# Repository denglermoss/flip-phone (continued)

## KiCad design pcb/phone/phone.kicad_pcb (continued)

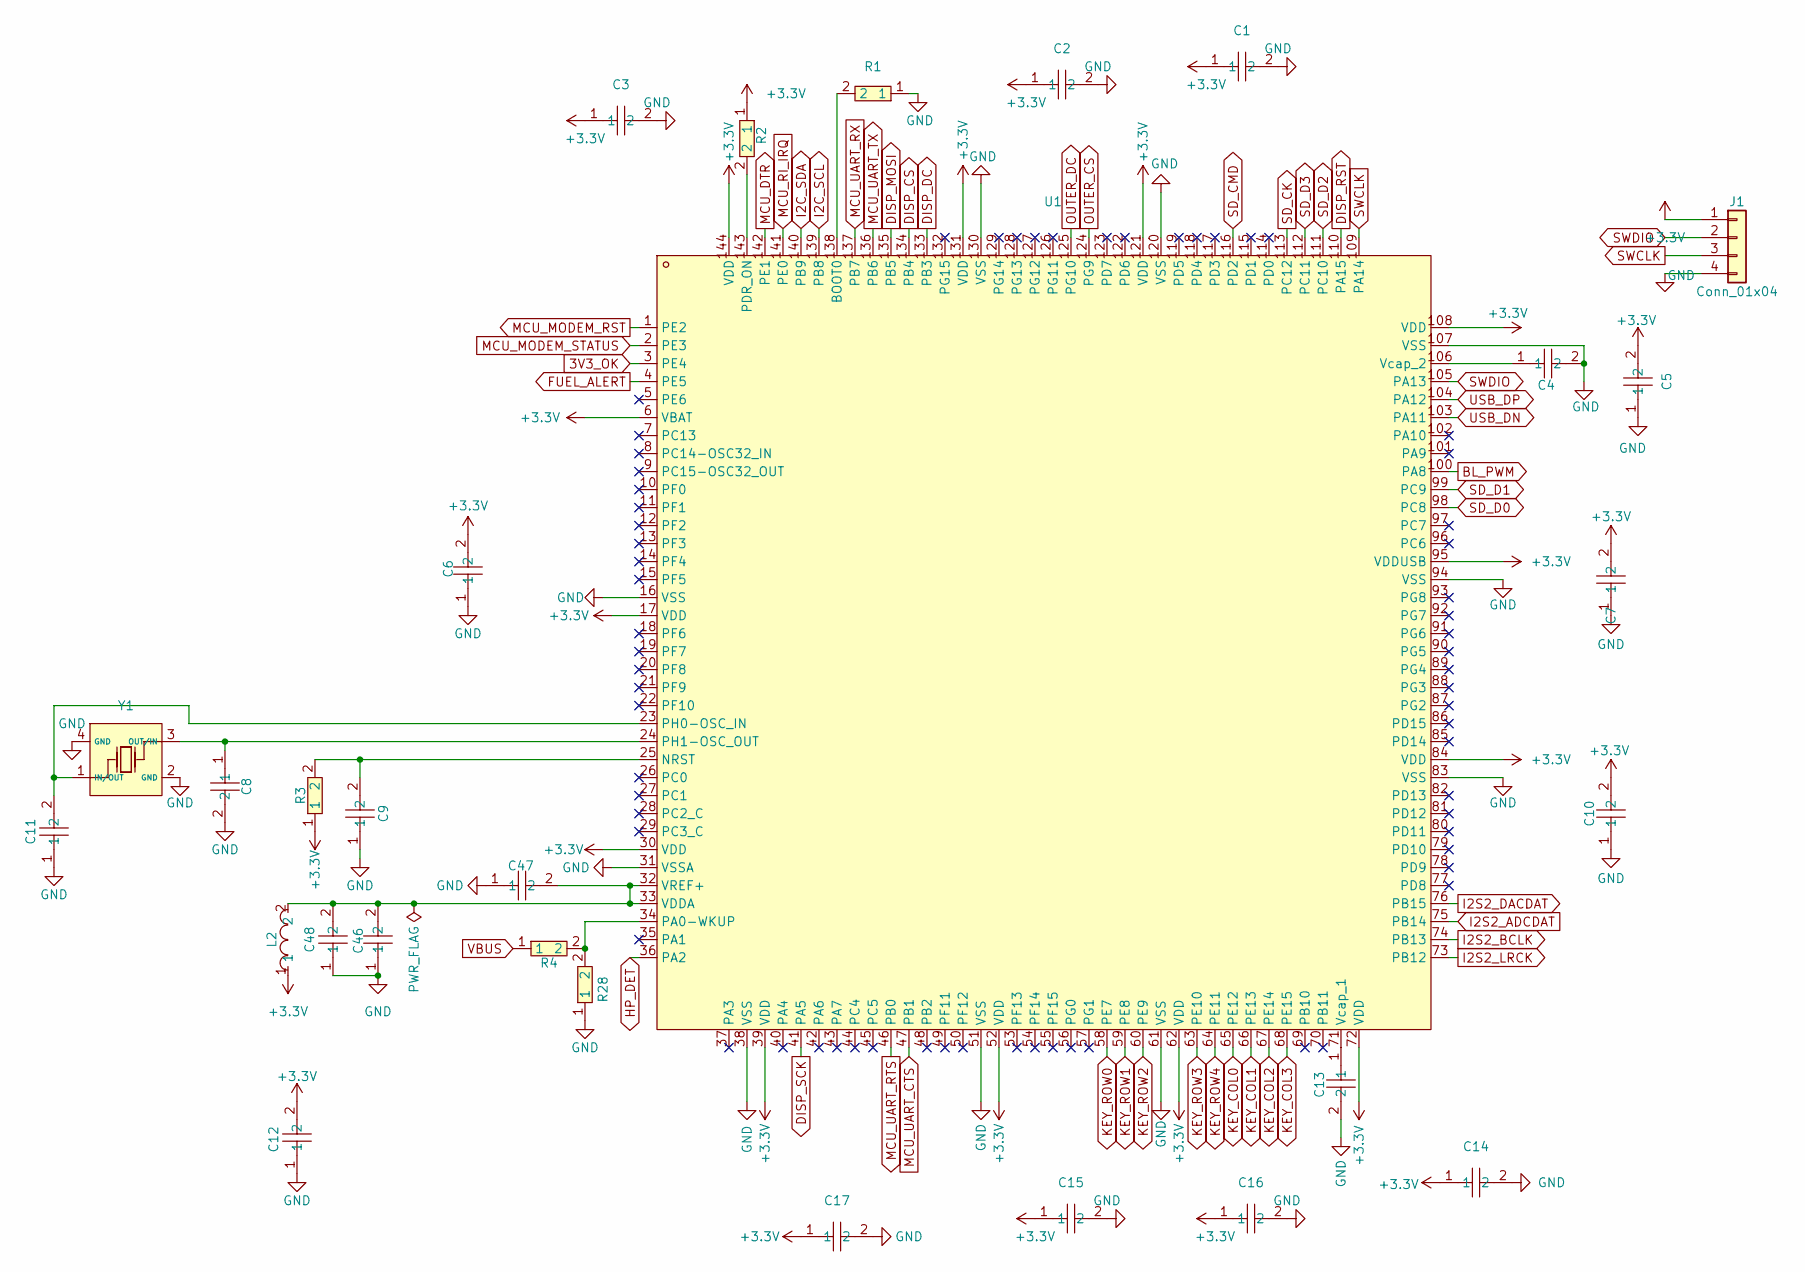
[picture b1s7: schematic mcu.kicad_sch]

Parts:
C1, C2, C3, C5, C6, C7, C9, C10, C12, C14, C15, C16, C17: 100nF; C0603
C4, C13: 2.2uF; C0603
C8, C11: 22pF; C0603
C46, C47: CC0603KRX7R9BB104; C0603; MPN CC0603KRX7R9BB104; LCSC Part C14663
C48: 1uF; C0603; MPN GRM188R61C105KA93D; LCSC Part C77404
J1: Conn_01x04; PinHeader_1x04_P2.54mm_Vertical
L2: BLM18KG601SN1D; L0603; MPN BLM18KG601SN1D; LCSC Part C85833
R1, R2, R3: 10k; C0603
R4: 100k; R0603
R28: RC0603FR-0768KL; R0603; MPN RC0603FR-0768KL; LCSC Part C114633
U1: STM32H743ZIT6; LQFP-144_L20.0-W20.0-P0.50-LS22.0-BL
Y1: ECS-80-12-33Q-GN-TR; CRYSTAL-SMD_4P-L3.2-W2.5-BL

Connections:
3V3_OK: U1.3 (PE4); also elsewhere on the board
+3.3V: C1.1, C2.1, C3.1, C5.2, C6.2, C7.2, C10.2, C12.2, C14.1, C15.1, C16.1, C17.1, J1.1, L2.1, R2.1, R3.1, U1.6 (VBAT), U1.17 (VDD), U1.30 (VDD), U1.39 (VDD), U1.52 (VDD), U1.62 (VDD), U1.72 (VDD), U1.84 (VDD), U1.95 (VDDUSB), U1.108 (VDD), U1.121 (VDD), U1.131 (VDD), U1.144 (VDD); also elsewhere on the board
BL_PWM: U1.100 (PA8); also elsewhere on the board
DISP_CS: U1.134 (PB4); also elsewhere on the board
DISP_DC: U1.133 (PB3); also elsewhere on the board
DISP_MOSI: U1.135 (PB5); also elsewhere on the board
DISP_RST: U1.110 (PA15); also elsewhere on the board
DISP_SCK: U1.41 (PA5); also elsewhere on the board
FUEL_ALERT: U1.4 (PE5); also elsewhere on the board
GND: C1.2, C2.2, C3.2, C4.2, C5.1, C6.1, C7.1, C8.2, C9.1, C10.1, C11.1, C12.1, C13.2, C14.2, C15.2, C16.2, C17.2, C46.1, C47.1, C48.1, J1.4, R1.1, R28.1, U1.16 (VSS), U1.31 (VSSA), U1.38 (VSS), U1.51 (VSS), U1.61 (VSS), U1.83 (VSS), U1.94 (VSS), U1.107 (VSS), U1.120 (VSS), U1.130 (VSS), Y1.2 (GND), Y1.4 (GND); also elsewhere on the board
HP_DET: U1.36 (PA2)
I2C_SCL: U1.139 (PB8); also elsewhere on the board
I2C_SDA: U1.140 (PB9); also elsewhere on the board
I2S2_ADCDAT: U1.75 (PB14); also elsewhere on the board
I2S2_BCLK: U1.74 (PB13); also elsewhere on the board
I2S2_DACDAT: U1.76 (PB15); also elsewhere on the board
I2S2_LRCK: U1.73 (PB12); also elsewhere on the board
KEY_COL0: U1.65 (PE12); also elsewhere on the board
KEY_COL1: U1.66 (PE13); also elsewhere on the board
KEY_COL2: U1.67 (PE14); also elsewhere on the board
KEY_COL3: U1.68 (PE15); also elsewhere on the board
KEY_ROW0: U1.58 (PE7); also elsewhere on the board
KEY_ROW1: U1.59 (PE8); also elsewhere on the board
KEY_ROW2: U1.60 (PE9); also elsewhere on the board
KEY_ROW3: U1.63 (PE10); also elsewhere on the board
KEY_ROW4: U1.64 (PE11); also elsewhere on the board
MCU_DTR: U1.142 (PE1); also elsewhere on the board
MCU_MODEM_RST: U1.1 (PE2); also elsewhere on the board
MCU_MODEM_STATUS: U1.2 (PE3); also elsewhere on the board
MCU_RI_IRQ: U1.141 (PE0); also elsewhere on the board
MCU_UART_CTS: U1.47 (PB1); also elsewhere on the board
MCU_UART_RTS: U1.46 (PB0); also elsewhere on the board
MCU_UART_RX: U1.137 (PB7); also elsewhere on the board
MCU_UART_TX: U1.136 (PB6); also elsewhere on the board
unnamed: R1.2, U1.138 (BOOT0)
unnamed: C9.2, R3.2, U1.25 (NRST)
unnamed: R4.2, R28.2, U1.34 (PA0-WKUP)
unnamed: R2.2, U1.143 (PDR_ON)
unnamed: C11.2, U1.23 (PH0-OSC_IN), Y1.1 (IN/OUT)
unnamed: C8.1, U1.24 (PH1-OSC_OUT), Y1.3 (OUT/IN)
unnamed: C46.2, C47.2, C48.2, L2.2, U1.32 (VREF+), U1.33 (VDDA)
unnamed: C13.1, U1.71 (Vcap_1)
unnamed: C4.1, U1.106 (Vcap_2)
OUTER_CS: U1.124 (PG9); also elsewhere on the board
OUTER_DC: U1.125 (PG10); also elsewhere on the board
SD_CK: U1.113 (PC12); also elsewhere on the board
SD_CMD: U1.116 (PD2); also elsewhere on the board
SD_D0: U1.98 (PC8); also elsewhere on the board
SD_D1: U1.99 (PC9); also elsewhere on the board
SD_D2: U1.111 (PC10); also elsewhere on the board
SD_D3: U1.112 (PC11); also elsewhere on the board
SWCLK: J1.3, U1.109 (PA14)
SWDIO: J1.2, U1.105 (PA13)
USB_DN: U1.103 (PA11); also elsewhere on the board
USB_DP: U1.104 (PA12); also elsewhere on the board
VBUS: R4.1; also elsewhere on the board

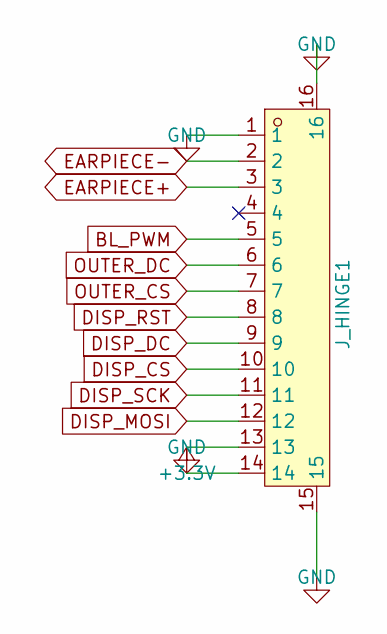
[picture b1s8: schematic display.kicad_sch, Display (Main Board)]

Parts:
J_HINGE1: 0.5K-HX-14PWB; FPC-SMD_14P-P0.50_HDGC_0.5K-HX-14PWB

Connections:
+3.3V: J_HINGE1.14; also elsewhere on the board
BL_PWM: J_HINGE1.5; also elsewhere on the board
DISP_CS: J_HINGE1.10; also elsewhere on the board
DISP_DC: J_HINGE1.9; also elsewhere on the board
DISP_MOSI: J_HINGE1.12; also elsewhere on the board
DISP_RST: J_HINGE1.8; also elsewhere on the board
DISP_SCK: J_HINGE1.11; also elsewhere on the board
EARPIECE+: J_HINGE1.3; also elsewhere on the board
EARPIECE-: J_HINGE1.2; also elsewhere on the board
GND: J_HINGE1.1, J_HINGE1.13, J_HINGE1.15, J_HINGE1.16; also elsewhere on the board
OUTER_CS: J_HINGE1.7; also elsewhere on the board
OUTER_DC: J_HINGE1.6; also elsewhere on the board

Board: 2 copper layers, 130 parts (0 on the bottom side), 104 nets, no tracks yet.

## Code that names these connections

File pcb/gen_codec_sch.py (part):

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    apw(net,px+off,py,90,f"#PWR{pwr_ctr}"); aw(px,py,px+off,py)

print("Wiring PCM/I2S-1...")
for pin,label,shape in [(30,"PCM_IN","output"),(31,"PCM_OUT","input"),(32,"PCM_SYNC","bidirectional"),(33,"PCM_CLK","bidirectional")]:
    px,py=u3p(pin); aw(px,py,px+7.06,py); agl(label,px+7.06,py,0,shape)

print("Wiring I2C...")
for pin,label in [(35,"I2C_SCL"),(36,"I2C_SDA")]:
    px,py=u3p(pin); aw(px,py,px+7.06,py); agl(label,px+7.06,py,0,"bidirectional")
for rx,ry,label in [(R12_X,R12_Y,"I2C_SCL"),(R13_X,R13_Y,"I2C_SDA")]:
    p1=cpp(rx,ry,1); p2=cpp(rx,ry,2)
    apw("+1V8",p1[0],p1[1]-5.08,0,f"#PWR{pwr_ctr}"); aw(p1[0],p1[1],p1[0],p1[1]-5.08)
    aw(p2[0],p2[1],p2[0]+5.08,p2[1]); agl(label,p2[0]+5.08,p2[1],0,"bidirectional")
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for cp,tx,bx in [(29,1,180),(28,3,185),(27,4,190),(26,5,195)]:
    cx,cy=u3p(cp); ax,ay=u9p(tx)
    aw(cx,cy,bx,cy); aw(bx,cy,bx,ay); aw(bx,ay,ax,ay)
for tp,label,shape in [(20,"I2S2_BCLK","input"),(18,"I2S2_LRCK","input"),(17,"I2S2_DACDAT","input"),(16,"I2S2_ADCDAT","output")]:
    bx,by=u9p(tp); aw(bx,by,bx+7.62,by); agl(label,bx+7.62,by,0,shape)

print("Wiring TXB0108 power...")
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
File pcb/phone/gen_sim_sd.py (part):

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        comp += fpwr('power:GND', wx, py, 0, '#PWR%d' % pc, sp); pc += 1

    # === U10 (ESD for SIM) wiring ===
    # Pin 1 (IO1) -> USIM_DATA
    px, py = pin_pos(U10_X, U10_Y, ESD_PINS[1])
    wx = px - STUB
    wires += fw(px, py, wx, py)
    labels += fgl('USIM_DATA', 'bidirectional', wx, py, 180)

    # Pin 2 (GND)
    px, py = pin_pos(U10_X, U10_Y, ESD_PINS[2])
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    wires += fw(px, py, wx, py)
    comp += fpwr('power:GND', wx, py, 0, '#PWR%d' % pc, sp); pc += 1

    # Pin 3 (IO2) -> USIM_RST
    px, py = pin_pos(U10_X, U10_Y, ESD_PINS[3])
    wx = px - STUB
    wires += fw(px, py, wx, py)
    labels += fgl('USIM_RST', 'bidirectional', wx, py, 180)

    # Pin 4 (IO3) -> USIM_CLK
    px, py = pin_pos(U10_X, U10_Y, ESD_PINS[4])
    wx = px + STUB
    wires += fw(px, py, wx, py)
    labels += fgl('USIM_CLK', 'bidirectional', wx, py, 0)

    # Pin 5 (IO4) -> USIM_VDD
    px, py = pin_pos(U10_X, U10_Y, ESD_PINS[5])
    wx = px + STUB
    wires += fw(px, py, wx, py)
    labels += fgl('USIM_VDD', 'bidirectional', wx, py, 0)

    # Pin 6 (IO5) - no connect (unused)
    px, py = pin_pos(U10_X, U10_Y, ESD_PINS[6])
    ncs += fnc(px, py)

    # === C38 (SIM decoupling) wiring ===
    # Pin 1 (top, original offset -5.08,0 with rot 90 -> above center) -> USIM_VDD
    px, py = pin_pos(C38_X, C38_Y, (-5.08, 0), 90)
    wy = py - STUB
    wires += fw(px, py, px, wy)
    labels += fgl('USIM_VDD', 'bidirectional', px, wy, 90)

    # Pin 2 (bottom, original offset 5.08,0 with rot 90 -> below center) -> GND
    px, py = pin_pos(C38_X, C38_Y, (5.08, 0), 90)
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    comp += fpwr('power:GND', px, wy, 0, '#PWR%d' % pc, sp); pc += 1

    # === R15 (SIM data pull-up) wiring ===
    # Pin 1 (left) -> USIM_VDD
    px, py = pin_pos(R15_X, R15_Y, (-5.08, 0), 0)
    wx = px - STUB
    wires += fw(px, py, wx, py)
    labels += fgl('USIM_VDD', 'bidirectional', wx, py, 180)

    # Pin 2 (right) -> USIM_DATA
    px, py = pin_pos(R15_X, R15_Y, (5.08, 0), 0)
    wx = px + STUB
    wires += fw(px, py, wx, py)
    labels += fgl('USIM_DATA', 'bidirectional', wx, py, 0)

    # === SD connector wiring ===
    # J_SD left pins (signals)
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        comp += fpwr('power:GND', wx, py, 0, '#PWR%d' % pc, sp); pc += 1

    # === U11 (ESD for SD) wiring ===
    # Pin 1 (IO1) -> SD_D0
    px, py = pin_pos(U11_X, U11_Y, ESD_PINS[1])
    wx = px - STUB
    wires += fw(px, py, wx, py)
    labels += fgl('SD_D0', 'bidirectional', wx, py, 180)

    # Pin 2 (GND)
    px, py = pin_pos(U11_X, U11_Y, ESD_PINS[2])
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    wires += fw(px, py, wx, py)
    comp += fpwr('power:GND', wx, py, 0, '#PWR%d' % pc, sp); pc += 1

    # Pin 3 (IO2) -> SD_D1
    px, py = pin_pos(U11_X, U11_Y, ESD_PINS[3])
    wx = px - STUB
    wires += fw(px, py, wx, py)
    labels += fgl('SD_D1', 'bidirectional', wx, py, 180)

    # Pin 4 (IO3) -> SD_D2
    px, py = pin_pos(U11_X, U11_Y, ESD_PINS[4])
    wx = px + STUB
    wires += fw(px, py, wx, py)
    labels += fgl('SD_D2', 'bidirectional', wx, py, 0)

    # Pin 5 (IO4) -> SD_D3
    px, py = pin_pos(U11_X, U11_Y, ESD_PINS[5])
    wx = px + STUB
    wires += fw(px, py, wx, py)
    labels += fgl('SD_D3', 'bidirectional', wx, py, 0)

    # Pin 6 (IO5) -> SD_CMD
    px, py = pin_pos(U11_X, U11_Y, ESD_PINS[6])
    wx = px + STUB
    wires += fw(px, py, wx, py)
    labels += fgl('SD_CMD', 'bidirectional', wx, py, 0)

    # === C39 (SD decoupling) wiring ===
    # Pin 1 (top, original offset -5.08,0 with rot 90 -> above center) -> +3.3V
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
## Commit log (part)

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2026-06-28 Initial project documentation: requirements, constraints, research notes, project log
2026-06-28 Add problem definition doc, update requirements and project log with resolved decisions
2026-06-28 Defer form factor/mechanical design — remove flip-specific assumptions from all docs
2026-06-28 Document modular ecosystem vision and USB interconnect constraint
    Add long-term vision of phone as hub for personal ecosystem of targeted
    devices (car system, etc.). Phone remains primary project. USB selected
    as primary interconnect for docked modules. MCU selection now constrained
    to require USB capability. Ecosystem module design explicitly out of scope.
2026-06-28 Add user background, ecosystem MCU risk analysis, feature wishlist; remove remaining flip references from research notes and project log
